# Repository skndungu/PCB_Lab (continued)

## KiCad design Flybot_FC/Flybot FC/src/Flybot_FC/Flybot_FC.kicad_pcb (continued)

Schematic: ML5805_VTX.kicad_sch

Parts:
AE1: MMCX; U.FL_Hirose_U.FL-R-SMT-1_Vertical
C27, C38, C44, C47: 2.2u; C_0402_1005Metric
C28, C29, C45, C48, C54, C58, C86: 100n; C_0402_1005Metric
C31, C32, C50, C52, C55: 1.2p; C_0402_1005Metric
C33: 500n; C_0402_1005Metric
C34, C35: 470p; C_0402_1005Metric
C36: 10n; C_0402_1005Metric
C37: 470n; C_0402_1005Metric
C39: 22n; C_0402_1005Metric
C40: 10p; C_0402_1005Metric
C41: 220p; C_0402_1005Metric
C42, C57: 680p; C_0402_1005Metric
C43, C46, C49, C51, C53, C56: 220n; C_0402_1005Metric
L2, L3: 3.9nH; L_0402_1005Metric
R14, R15: 10k; R_0402_1005Metric
R16: 16.5R; R_0402_1005Metric
R17: 383R; R_0402_1005Metric
R18: 750R; R_0402_1005Metric
R19: 10R; R_0402_1005Metric
R20: 402R; R_0402_1005Metric
R21: 1.2k; R_0402_1005Metric
TP6, TP7, TP8, TP9, TP10, TP11, TP12: TestPoint; TestPoint_Pad_D1.0mm
U3: ML5805DM; QFN-40-1EP_6x6mm_P0.5mm_EP4.6x4.6mm
X1: LFB215G37SG8A180; BPF2012LL01R5000A

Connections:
+3V3: C27.1, C28.1, C29.1, C47.1, C48.1, C86.1, R14.1, U3.9 (VDD), U3.19 (VCCPLL), U3.27 (VCCA), U3.31 (VCC_PA); also elsewhere on the board
/MAX7456_OSD/DATA.OUT: R16.1; also elsewhere on the board
/ML5805_VTX/VREGPA: C54.1, C55.1, L2.2, U3.32 (VREGPA)
/ML5805_VTX/VTX.CLK: U3.8 (CLK); also elsewhere on the board
/ML5805_VTX/VTX.CS: U3.6 (EN); also elsewhere on the board
/ML5805_VTX/VTX.SDO: U3.7 (DATA); also elsewhere on the board
/ML5805_VTX/VTX.XCEN: R14.2, U3.1 (XCEN); also elsewhere on the board
GND: AE1.2 (Shield), C27.2, C28.2, C29.2, C33.2, C34.2, C37.2, C38.2, C39.2, C40.2, C41.2, C42.2, C43.2, C44.2, C45.2, C46.2, C47.2, C48.2, C49.2, C50.2, C51.2, C52.2, C53.2, C54.2, C55.2, C56.2, C57.2, C58.2, C86.2, L3.2, R15.1, R17.1, R21.2, U3.5 (VSSD), U3.41 (EPAD), X1.1 (GND), X1.3 (GND); also elsewhere on the board
unnamed: AE1.1 (A), C32.2, L3.1
unnamed: C35.2, TP11.1
unnamed: C36.2, R18.1, R21.1
unnamed: C41.1, R19.2, R20.1
unnamed: TP9.1, U3.37 (AOUT)
unnamed: TP12.1, U3.39 (DATASEL)
unnamed: C34.1, R16.2, U3.4 (DIN)
unnamed: TP10.1, U3.38 (DOUT)
unnamed: C35.1, U3.12 (FREF)
unnamed: R17.2, U3.29 (ISET)
unnamed: R18.2, U3.14 (PLL_SW)
unnamed: C36.1, C42.1, R20.2, U3.15 (QPO)
unnamed: TP8.1, U3.36 (RSSI)
unnamed: R15.2, U3.2 (RXON)
unnamed: TP6.1, U3.34 (TPI)
unnamed: TP7.1, U3.35 (TPQ)
unnamed: C31.1, C33.1, L2.1, U3.28 (TXO)
unnamed: C39.1, U3.11 (VBG_1P8)
unnamed: C53.1, U3.30 (VBG_PA)
unnamed: C38.1, C45.1, U3.25 (VBG_RF)
unnamed: C37.1, U3.20 (VBG_VCO)
unnamed: C44.1, C58.1, U3.13 (VCCSYN), U3.18 (VREGPLL)
unnamed: C46.1, U3.33 (VREGIF)
unnamed: C51.1, C52.1, U3.21 (VREGLNA)
unnamed: C49.1, C50.1, U3.24 (VREGRX), U3.26 (VREGTX)
unnamed: C43.1, C57.1, U3.17 (VREGVCO)
unnamed: C56.1, U3.10 (VREG_1P8)
unnamed: C40.1, R19.1, U3.16 (VTUNE)
unnamed: C31.2, X1.2 (IN)
unnamed: C32.1, X1.4 (OUT)

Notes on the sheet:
5.8GHZ VARIABLE DATA RATE FSK TRANSCEIVER WITH INTEGRATED PA

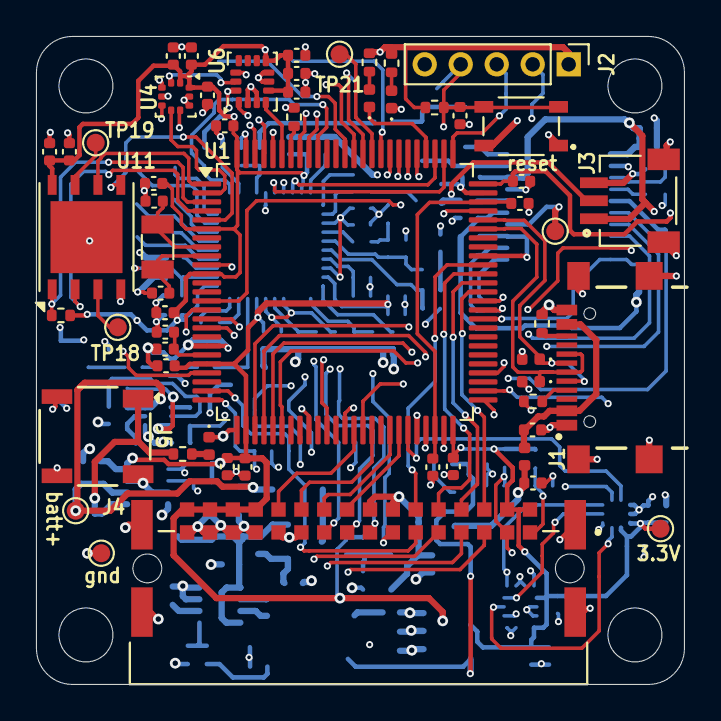
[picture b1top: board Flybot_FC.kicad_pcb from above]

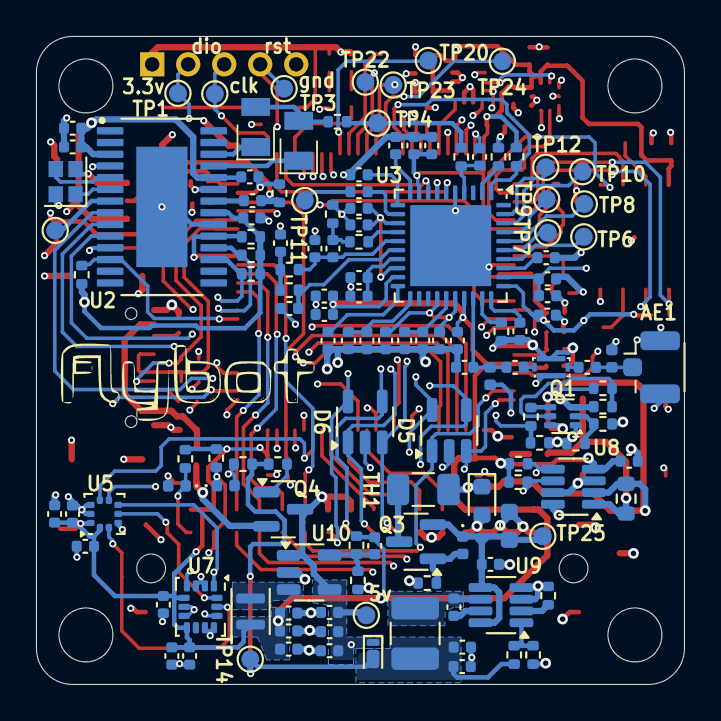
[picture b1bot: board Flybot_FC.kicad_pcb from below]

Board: 4 copper layers, 36.0 x 36.0 mm, 196 parts (135 on the bottom side), 135 nets.

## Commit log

2026-01-26 Flybot_FC repository
2026-01-27 schematic review
2026-01-28 Bill of materials
2026-02-05 Final Flybot_FC
